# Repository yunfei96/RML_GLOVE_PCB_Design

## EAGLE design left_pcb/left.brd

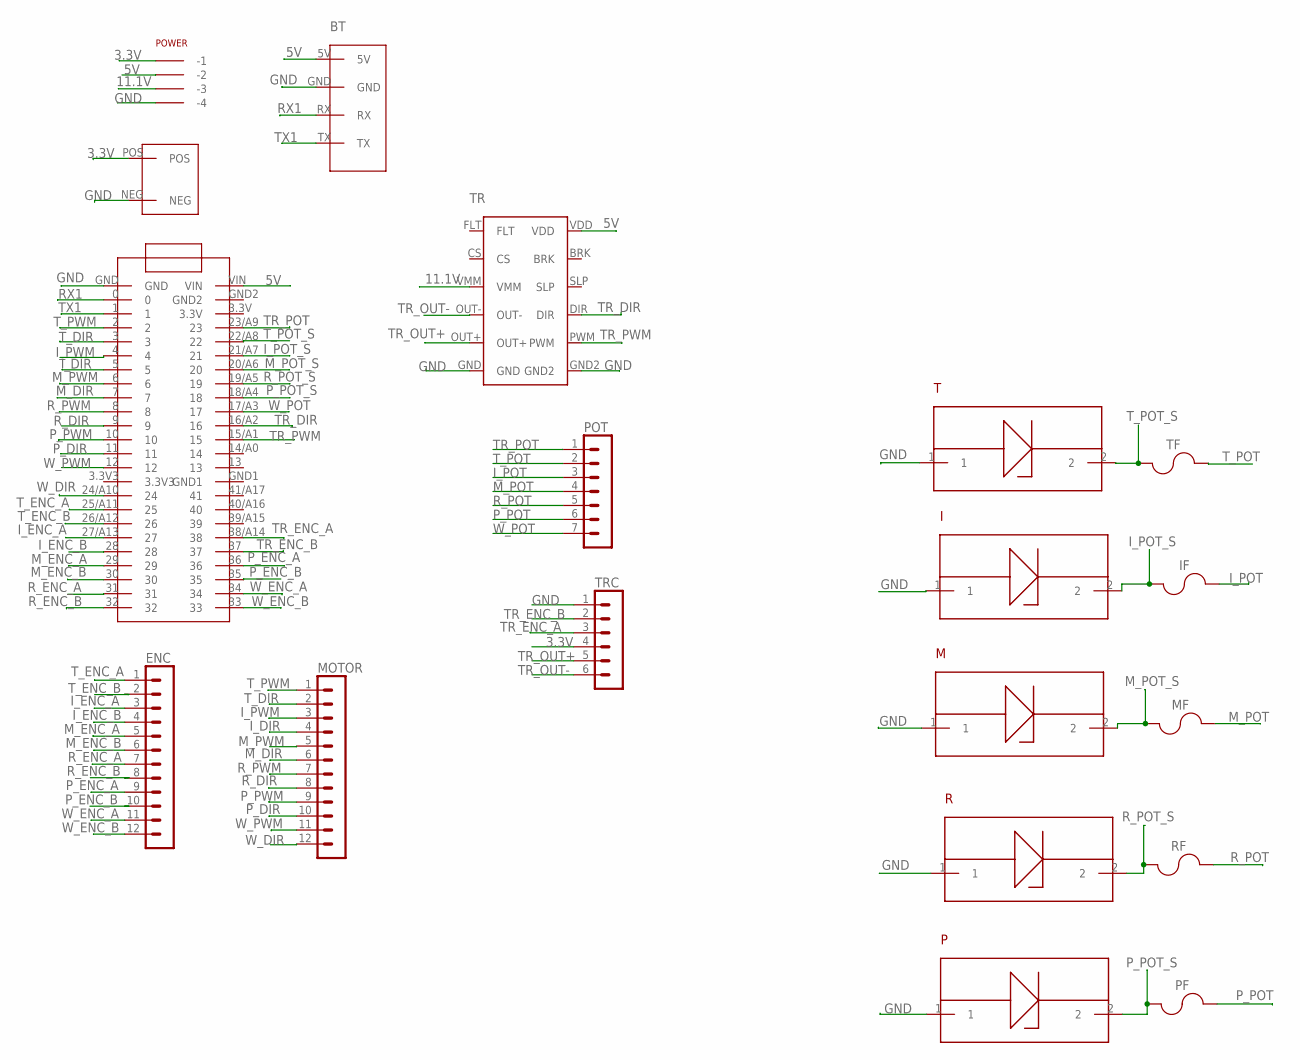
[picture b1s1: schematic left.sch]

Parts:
4.1B: TEENSY_4.1_DIL
ANG: 2; 2_PIN_SMALL
BT: 2; 4_PIN_SMALL
ENC: 53047-1210
I: BZX584C_ZENER_DIODE; SOD-523
IF: 0805D; 0805
M: BZX584C_ZENER_DIODE; SOD-523
MF: 0805D; 0805
MOTOR: 53047-1210
P: BZX584C_ZENER_DIODE; SOD-523
PF: 0805D; 0805
POT: 53047-0710
POWER: 5267-4
R: BZX584C_ZENER_DIODE; SOD-523
RF: 0805D; 0805
T: BZX584C_ZENER_DIODE; SOD-523
TF: 0805D; 0805
TR: DRV8801
TRC: 53047-0610

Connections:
3.3V: ANG.POS, POWER.P$1 (-1), TRC.4
5V: 4.1B.VIN, BT.5V, POWER.P$2 (-2), TR.VDD
11.1V: POWER.P$3 (-3), TR.VMM
GND: 4.1B.GND, ANG.NEG, BT.GND, I.1, M.1, P.1, POWER.P$4 (-4), R.1, T.1, TR.GND, TR.GND2, TRC.1
I_DIR: 4.1B.5, MOTOR.4
I_ENC_A: 4.1B.27/A13 (27), ENC.3
I_ENC_B: 4.1B.28, ENC.4
I_POT: IF.2, POT.3
I_POT_S: 4.1B.21/A7 (21), I.2, IF.1
I_PWM: 4.1B.4, MOTOR.3
M_DIR: 4.1B.7, MOTOR.6
M_ENC_A: 4.1B.29, ENC.5
M_ENC_B: 4.1B.30, ENC.6
M_POT: MF.2, POT.4
M_POT_S: 4.1B.20/A6 (20), M.2, MF.1
M_PWM: 4.1B.6, MOTOR.5
P_DIR: 4.1B.11, MOTOR.10
P_ENC_A: 4.1B.36, ENC.9
P_ENC_B: 4.1B.35, ENC.10
P_POT: PF.2, POT.6
P_POT_S: 4.1B.18/A4 (18), P.2, PF.1
P_PWM: 4.1B.10, MOTOR.9
RX1: 4.1B.0, BT.RX
R_DIR: 4.1B.9, MOTOR.8
R_ENC_A: 4.1B.31, ENC.7
R_ENC_B: 4.1B.32, ENC.8
R_POT: POT.5, RF.2
R_POT_S: 4.1B.19/A5 (19), R.2, RF.1
R_PWM: 4.1B.8, MOTOR.7
TR_DIR: 4.1B.16/A2 (16), TR.DIR
TR_ENC_A: 4.1B.38/A14 (38), TRC.3
TR_ENC_B: 4.1B.37, TRC.2
TR_OUT+: TR.OUT+, TRC.5
TR_OUT-: TR.OUT-, TRC.6
TR_POT: 4.1B.23/A9 (23), POT.1
TR_PWM: 4.1B.15/A1 (15), TR.PWM
TX1: 4.1B.1, BT.TX
T_DIR: 4.1B.3, MOTOR.2
T_ENC_A: 4.1B.25/A11 (25), ENC.1
T_ENC_B: 4.1B.26/A12 (26), ENC.2
T_POT: POT.2, TF.2
T_POT_S: 4.1B.22/A8 (22), T.2, TF.1
T_PWM: 4.1B.2, MOTOR.1
W_DIR: 4.1B.24/A10 (24), MOTOR.12
W_ENC_A: 4.1B.34, ENC.11
W_ENC_B: 4.1B.33, ENC.12
W_POT: 4.1B.17/A3 (17), POT.7
W_PWM: 4.1B.12, MOTOR.11

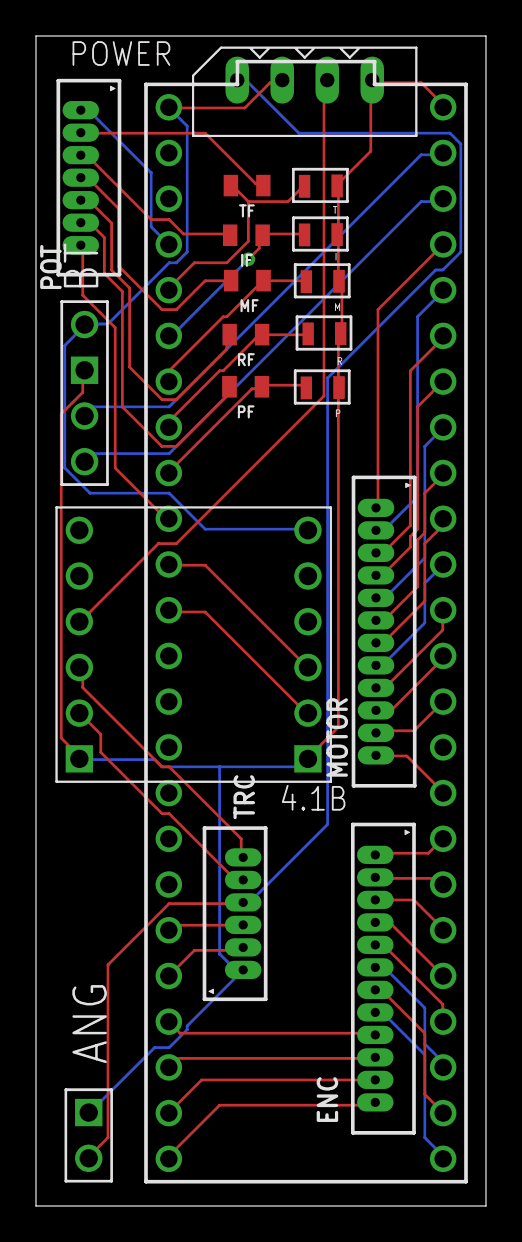
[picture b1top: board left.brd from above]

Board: 2 copper layers, 25.0 x 65.0 mm, 19 parts (0 on the bottom side), 48 nets.

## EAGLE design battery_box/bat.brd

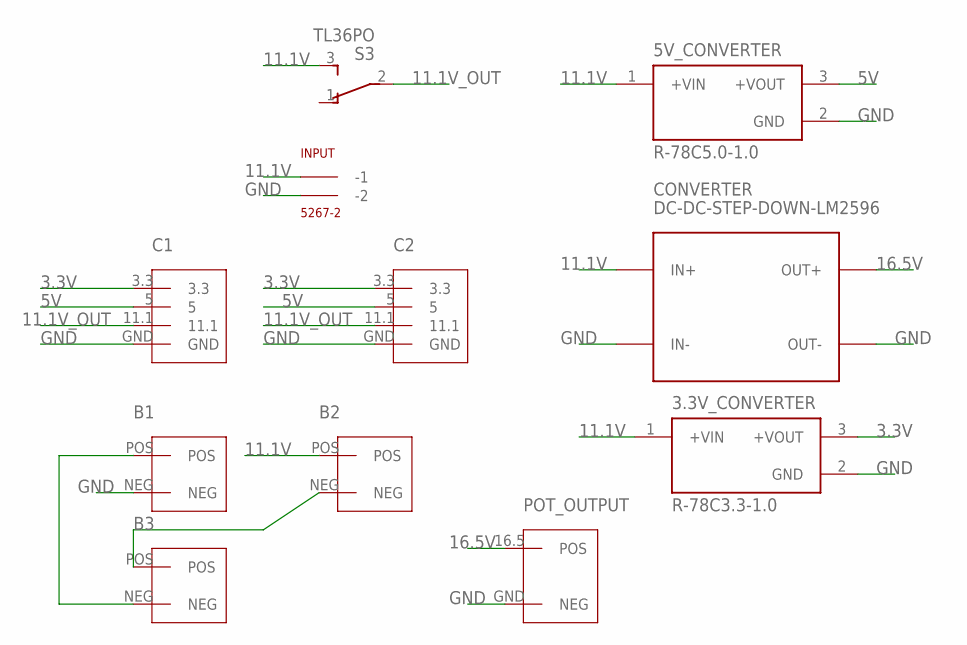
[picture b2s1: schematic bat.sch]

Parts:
3.3V_CONVERTER: R-78C3.3-1.0; CONV_R-78C5.0-1.0
5V_CONVERTER: R-78C5.0-1.0; CONV_R-78C5.0-1.0
B1, B2, B3: 2_PIN_WIRE
C1, C2: 4_PIN_WIRE
CONVERTER: DC-DC-STEP-DOWN-LM2596
INPUT: 5267-2
POT_OUTPUT: 2_PIN_SMALL
S3: TL36PO; TL3XPO

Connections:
3.3V: 3.3V_CONVERTER.3 (+VOUT), C1.3.3, C2.3.3
5V: 5V_CONVERTER.3 (+VOUT), C1.5, C2.5
11.1V: 3.3V_CONVERTER.1 (+VIN), 5V_CONVERTER.1 (+VIN), B2.POS, CONVERTER.IN+, INPUT.P$1 (-1), S3.3 (S)
11.1V_OUT: C1.11.1, C2.11.1, S3.2
16.5V: CONVERTER.OUT+, POT_OUTPUT.16.5 (POS)
GND: 3.3V_CONVERTER.2 (GND), 5V_CONVERTER.2 (GND), B1.NEG, C1.GND, C2.GND, CONVERTER.IN-, CONVERTER.OUT-, INPUT.P$2 (-2), POT_OUTPUT.GND (NEG)
unnamed: B1.POS, B3.NEG
unnamed: B2.NEG, B3.POS

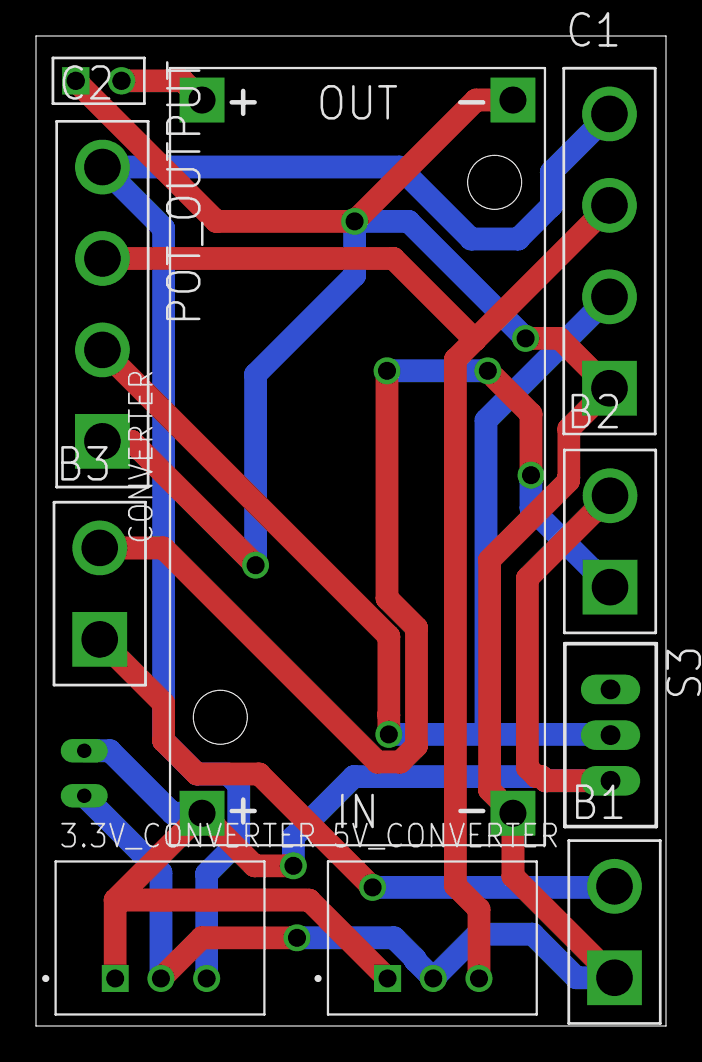
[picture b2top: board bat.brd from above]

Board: 2 copper layers, 35.0 x 55.0 mm, 11 parts (1 on the bottom side), 8 nets.

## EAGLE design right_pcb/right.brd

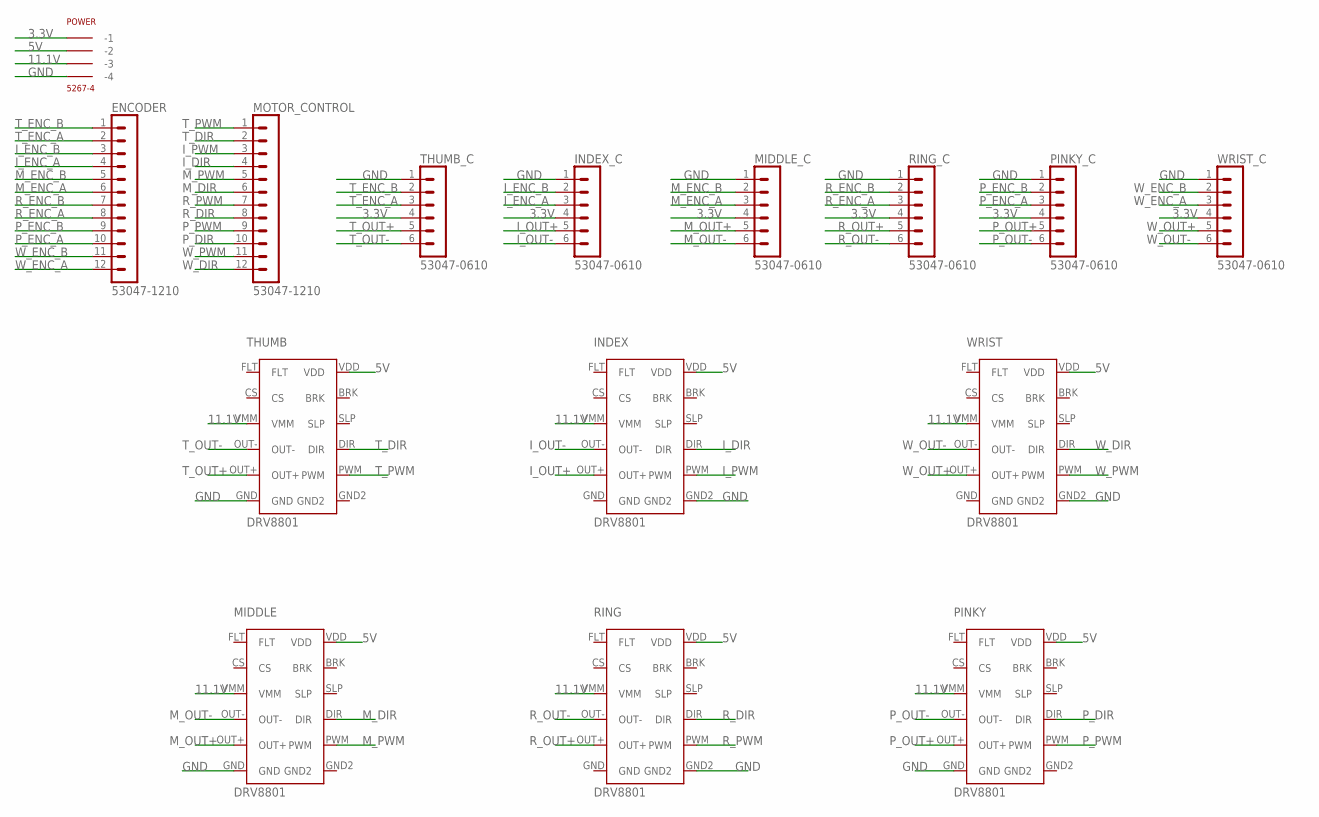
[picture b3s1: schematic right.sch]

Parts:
ENCODER: 53047-1210
INDEX: DRV8801
INDEX_C: 53047-0610
MIDDLE: DRV8801
MIDDLE_C: 53047-0610
MOTOR_CONTROL: 53047-1210
PINKY: DRV8801
PINKY_C: 53047-0610
POWER: 5267-4
RING: DRV8801
RING_C: 53047-0610
THUMB: DRV8801
THUMB_C: 53047-0610
WRIST: DRV8801
WRIST_C: 53047-0610

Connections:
3.3V: INDEX_C.4, MIDDLE_C.4, PINKY_C.4, POWER.P$1 (-1), RING_C.4, THUMB_C.4, WRIST_C.4
5V: INDEX.VDD, MIDDLE.VDD, PINKY.VDD, POWER.P$2 (-2), RING.VDD, THUMB.VDD, WRIST.VDD
11.1V: INDEX.VMM, MIDDLE.VMM, PINKY.VMM, POWER.P$3 (-3), RING.VMM, THUMB.VMM, WRIST.VMM
GND: INDEX.GND2, INDEX_C.1, MIDDLE.GND, MIDDLE_C.1, PINKY.GND, PINKY_C.1, POWER.P$4 (-4), RING.GND2, RING_C.1, THUMB.GND, THUMB_C.1, WRIST.GND2, WRIST_C.1
I_DIR: INDEX.DIR, MOTOR_CONTROL.4
I_ENC_A: ENCODER.4, INDEX_C.3
I_ENC_B: ENCODER.3, INDEX_C.2
I_OUT+: INDEX.OUT+, INDEX_C.5
I_OUT-: INDEX.OUT-, INDEX_C.6
I_PWM: INDEX.PWM, MOTOR_CONTROL.3
M_DIR: MIDDLE.DIR, MOTOR_CONTROL.6
M_ENC_A: ENCODER.6, MIDDLE_C.3
M_ENC_B: ENCODER.5, MIDDLE_C.2
M_OUT+: MIDDLE.OUT+, MIDDLE_C.5
M_OUT-: MIDDLE.OUT-, MIDDLE_C.6
M_PWM: MIDDLE.PWM, MOTOR_CONTROL.5
P_DIR: MOTOR_CONTROL.10, PINKY.DIR
P_ENC_A: ENCODER.10, PINKY_C.3
P_ENC_B: ENCODER.9, PINKY_C.2
P_OUT+: PINKY.OUT+, PINKY_C.5
P_OUT-: PINKY.OUT-, PINKY_C.6
P_PWM: MOTOR_CONTROL.9, PINKY.PWM
R_DIR: MOTOR_CONTROL.8, RING.DIR
R_ENC_A: ENCODER.8, RING_C.3
R_ENC_B: ENCODER.7, RING_C.2
R_OUT+: RING.OUT+, RING_C.5
R_OUT-: RING.OUT-, RING_C.6
R_PWM: MOTOR_CONTROL.7, RING.PWM
T_DIR: MOTOR_CONTROL.2, THUMB.DIR
T_ENC_A: ENCODER.2, THUMB_C.3
T_ENC_B: ENCODER.1, THUMB_C.2
T_OUT+: THUMB.OUT+, THUMB_C.5
T_OUT-: THUMB.OUT-, THUMB_C.6
T_PWM: MOTOR_CONTROL.1, THUMB.PWM
W_DIR: MOTOR_CONTROL.12, WRIST.DIR
W_ENC_A: ENCODER.12, WRIST_C.3
W_ENC_B: ENCODER.11, WRIST_C.2
W_OUT+: WRIST.OUT+, WRIST_C.5
W_OUT-: WRIST.OUT-, WRIST_C.6
W_PWM: MOTOR_CONTROL.11, WRIST.PWM

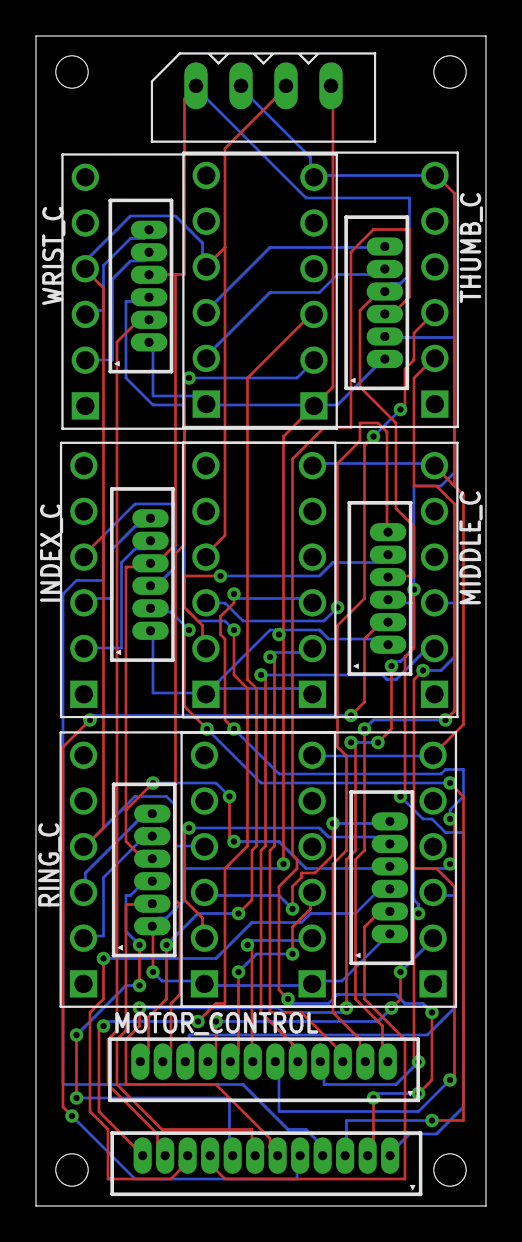
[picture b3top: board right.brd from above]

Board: 2 copper layers, 25.0 x 65.0 mm, 15 parts (0 on the bottom side), 40 nets.

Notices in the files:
parts and their libraries:
diy-modules: Released under the Creative Commons Attribution 4.0 International License: http://creativecommons.org/licenses/by/4.0
con-molex-picoblade: Copyright (C) 2010, Bob Starr
